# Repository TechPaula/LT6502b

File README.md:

# LT6502b
Second, slimmer, revision of my [LT6502](https://github.com/TechPaula/LT6502/tree/main) 6502 laptop.
This is very much a work in progress.

## Specs
* 65C02 running at 14MHz (hopefully)
* 46KByte of user RAM 
* EhBASIC 22p2
* eWOZMON
* Compact Flash for storage
* Built in battery (7400mAh currently)
* USB-PD Rechargable
* 10.1" Screen
* nanoSwinSID for sound (as well as beeps)

Features improved on since previous version;
* Better placement of keys
* Use an FFC for the display
* Simpler case
* Battery level indicator (CAPS Lock will flash when getting low)
* USB charge and data on single USB-C connector
* Single PCB for keyboard and logic/processor

## Images
2026-03-07 - Render of case design in progress

2026-03-21 - Picture of PCB mid assembly

## Updates
* 2026-03-21 - PCB assembly underway (power tests passed)
* 2026-03-07 - Case coming together, currently 31mm in height, vs the 70mm of the previous version)
* 2026-03-01 - PCB sent for manufacture

## In progress
* Board assembly
* Glue Logic

## To do
* Get larger display working (probably on PC6502 first)
* CPLD Glue logic working
* Firmware (removing the display parts for now as the new display uses a different driver chip)
* Keyboard/Modem code (needs a change due to using the chip directly and I need to add in serial port driver for Modem)
* Testing, lots of testing.
* Finish the case design and print it.

## Memory Map
The memory map is copied from the previous LT6502, with removal of expansion port and addition of Modem and SID

#### High Level
| Start | End | Size (Dec) | Size (Hex) | What is it | Notes |
|-------|-----|----|----|----|---------------|
| 0x0000|0xBEAF| 48816 | 0xBEB0 | RAM | This includes Zeropage and other bits BASIC may need (more below) |
| 0xBF00|0xBFFF| 512 | 0x200 | peripherals | This is where the peripherals are mapped (see below) |
| 0xC000|0xFFFF| 12288 | 0x3000 | ROM | holding EhBASIC, eWoz monitor, bootstrap and vectors |

##### ROM breakdown
| Start | End | Size (Dec) | Size (Hex) | What is it | Notes |
|-------|-----|----|----|----|---------------|
| 0xC000|0xFAFF| 15104 | 0x3B0 | EhBASIC | EhBASIC 2.22p5 |
| 0xF000|0xF2FF| 768 | 0x300 | eWozMon | [Enhanced Wozmon](https://gist.github.com/BigEd/2760560) |
| 0xF300|0xFFF9| 3322| 0xCFA | Bootstrap | startup messages and also input/output/load/save functions |
| 0xFFFA|0xFFFF| 6 | 0x0A | 6502 Vectors | |

##### RAM breakdown
| Start | End | Size (Dec) | Size (Hex) | What is it | Notes |
|-------|-----|----|----|----|---------------|
| 0x0000|0x02FF| 768 | 0x300 | RAM | This includes Zeropage and other bits BASIC may need |
| 0x0300|0x07FF| 1280 | 0x500 | RAM | This is going to be for the compact flash reading/writing |
| 0x0800|0xBDFF| 46592 | 0xB6B0 | ROM | BASIC RAM available |

##### peripherals
| Address | subAddr range | RW | What is it | Notes |
|-------|-----|----|----|---------------|
|0xBF00|00-1F|RW| nanoSwinSID | |
|0xBF20|0-1|RW| Modem | |
|0xBF30|30-9F|RW| Unused Currently | |
|0xBFAO|0-0| W| Beeper | just write 0xFF and 0x00 to turn on/off the speaker |
|0xBFBO|0-7|RW| Compact Flash |  |
|0xBFCO|0-F|RW| 65C22 |  on board VIA |
|0xBFDO|0-F|0-1| Display |   |
|0xBFEO|0-F|RW| Atmega644p | internal keyboard  |
|0xBFF0|0-1|RW| Console | FTDI USB console port   |

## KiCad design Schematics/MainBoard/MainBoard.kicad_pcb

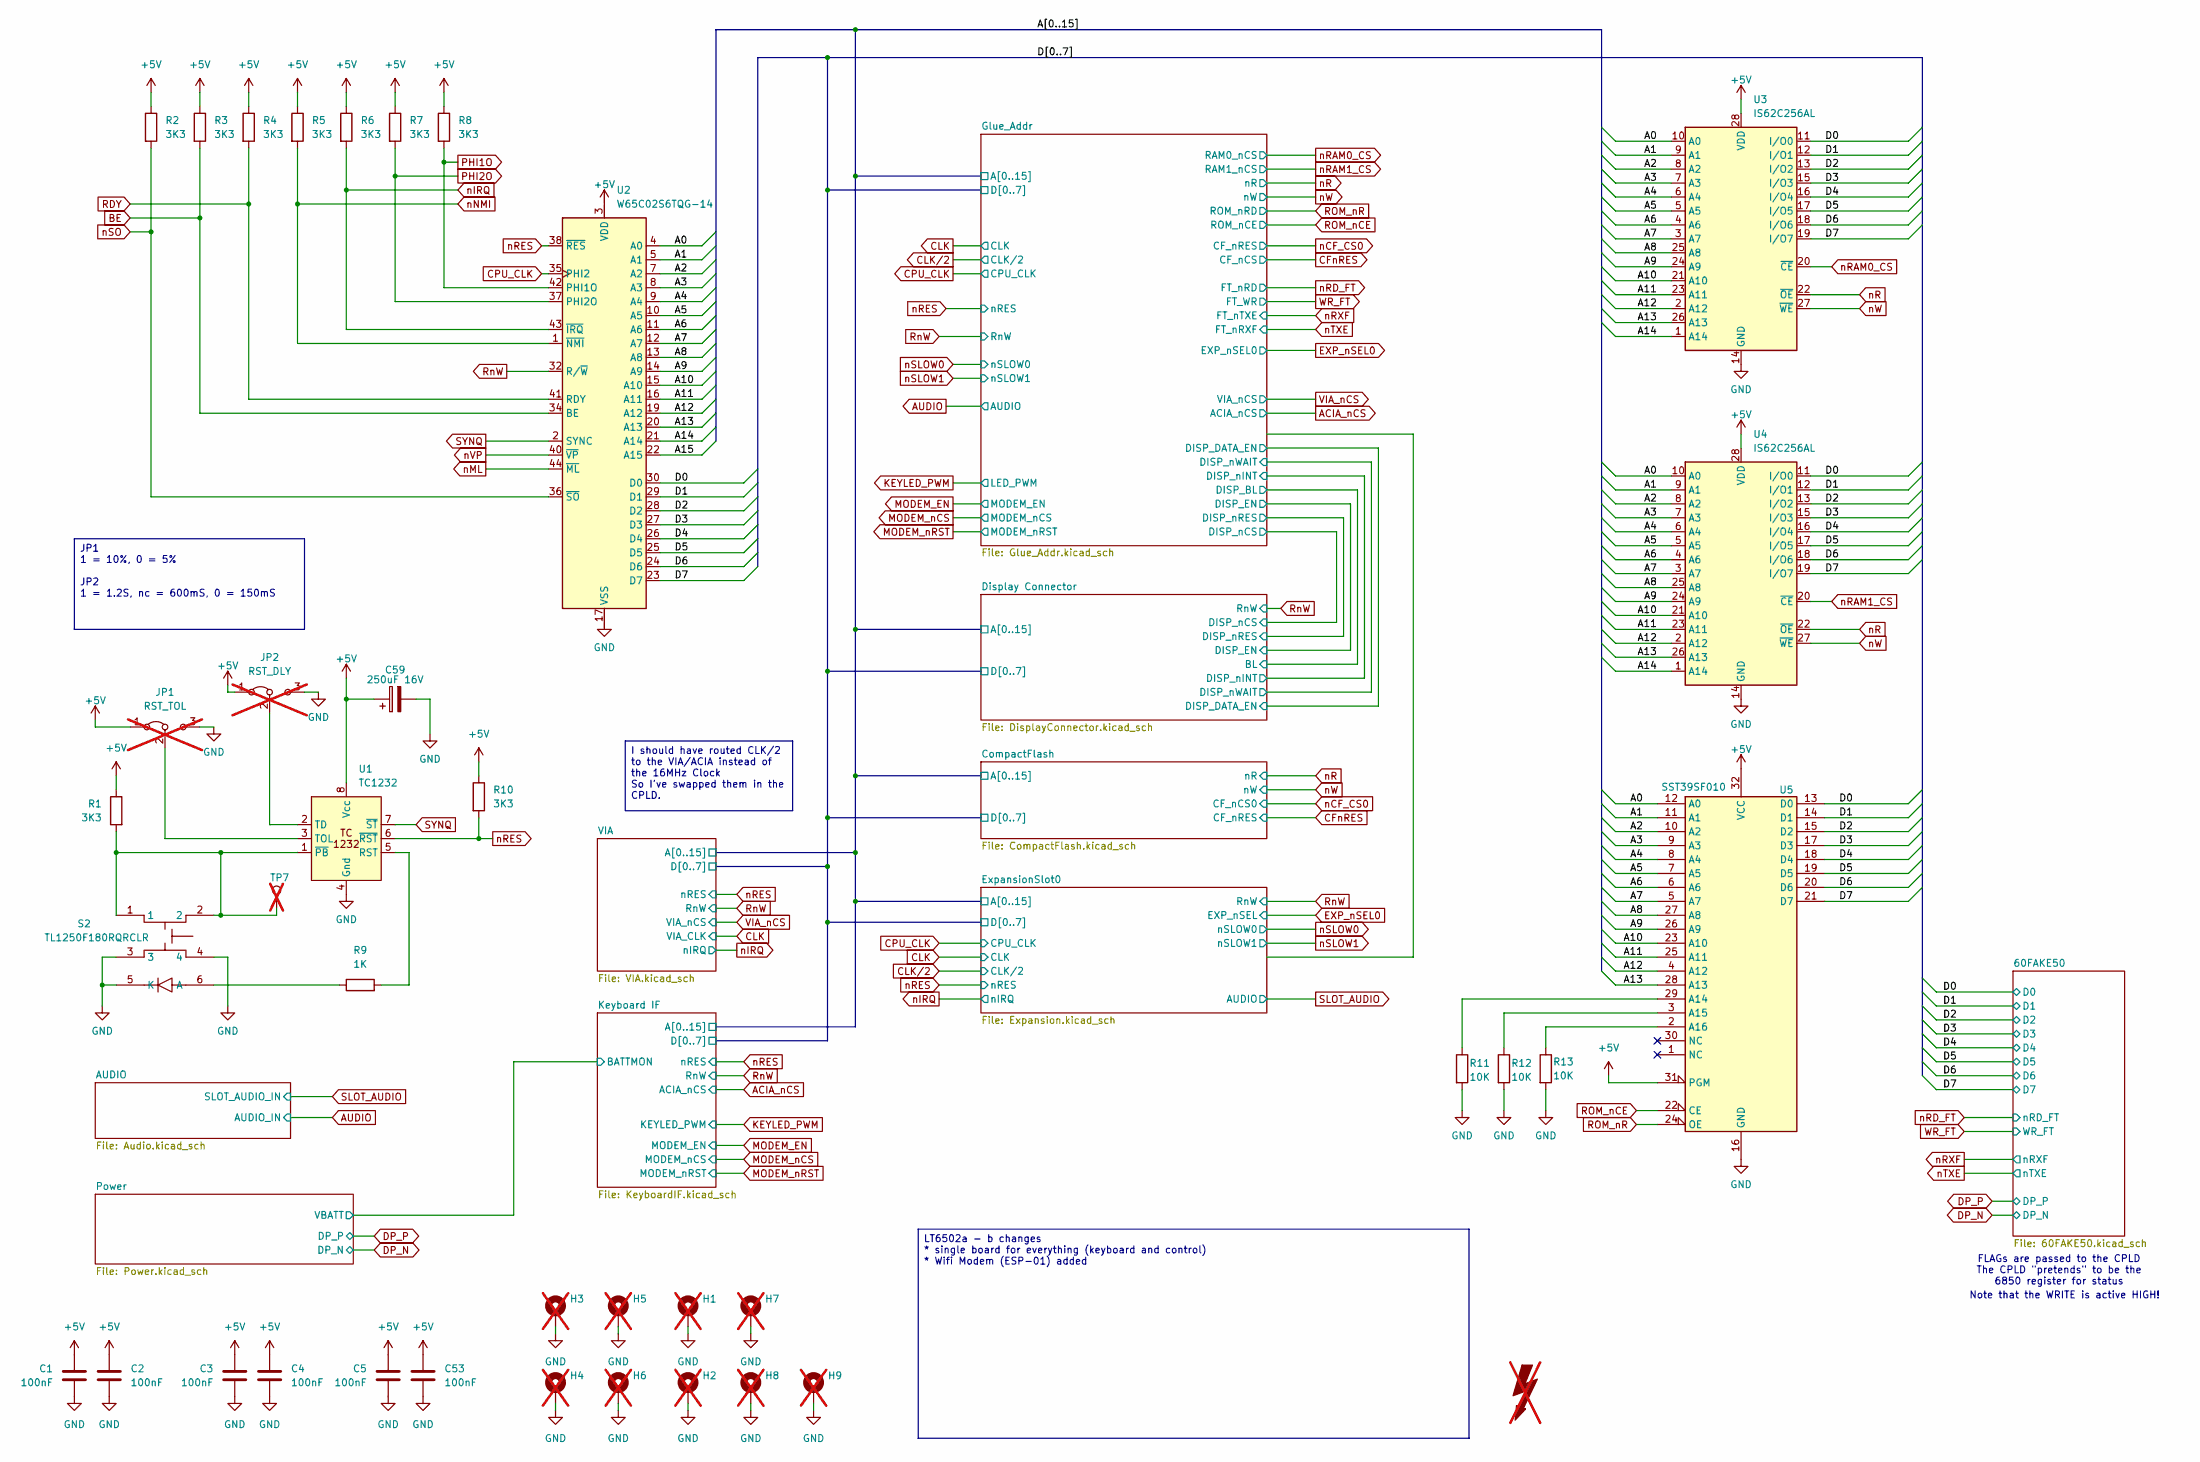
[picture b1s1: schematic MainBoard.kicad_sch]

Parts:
C1, C2, C3, C4, C5, C53: 100nF; C_0603_1608Metric; LCSC C113803
C59: 250uF 16V; CP_Elec_10x12.5; Mouser Part Number 667-EEV-FK1V681Q
FOX1: SYM_Flash_Large; Fox_avatar_18mm; LCSC DNF; not fitted
H1, H2, H3, H4, H5, H6, H7, H8, H9: MountingHole_Pad; MountingHole_3.2mm_M3_Pad_TopBottom; LCSC DNF; not fitted
JP1: RST_TOL; SolderJumper-3_P1.3mm_Bridged12_Pad1.0x1.5mm_NumberLabels; LCSC DNF; not fitted
JP2: RST_DLY; SolderJumper-3_P1.3mm_Bridged12_Pad1.0x1.5mm_NumberLabels; LCSC DNF; not fitted
R1, R2, R3, R4, R5, R6, R7, R8, R10: 3K3; R_0402_1005Metric; LCSC C25890
R9: 1K; R_0402_1005Metric; LCSC C11702
R11, R12, R13: 10K; R_0402_1005Metric; LCSC C25744
S2: TL1250F180RQRCLR; Mouser Part Number 612-TL1250F180RQRCLR
TP7: TestPoint; TestPoint_Loop_D1.80mm_Drill1.0mm_Beaded; LCSC DNF; not fitted
U1: TC1232; DIP-8_W7.62mm_LongPads; Mouser Part Number 579-TC1232CPA
U2: W65C02S6TQG-14; QFP80P1320X1320X270-44N; Mouser Part Number 955-W65C02S6TQG-14
U3, U4: IS62C256AL; SOP-28_8.4x18.16mm_P1.27mm; Mouser Part Number 870-62C256AL-25ULIT
U5: SST39SF010; DIP-32_W15.24mm_Socket; LCSC DNF

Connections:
+5V: C1.1, C2.1, C3.1, C4.1, C5.1, C53.1, C59.1, JP1.1 (A), JP2.1 (A), R1.1, R2.1, R3.1, R4.1, R5.1, R6.1, R7.1, R8.1, R10.1, U1.8 (Vcc), U2.3 (VDD), U2.31 (VDD), U3.28 (VDD), U4.28 (VDD), U5.31 (PGM), U5.32 (VCC); also elsewhere on the board
/A0: U2.4 (A0), U3.10 (A0), U4.10 (A0), U5.12 (A0); also elsewhere on the board
/A1: U2.5 (A1), U3.9 (A1), U4.9 (A1), U5.11 (A1); also elsewhere on the board
/A2: U2.7 (A2), U3.8 (A2), U4.8 (A2), U5.10 (A2); also elsewhere on the board
/A3: U2.8 (A3), U3.7 (A3), U4.7 (A3), U5.9 (A3); also elsewhere on the board
/A4: U2.9 (A4), U3.6 (A4), U4.6 (A4), U5.8 (A4); also elsewhere on the board
/A5: U2.10 (A5), U3.5 (A5), U4.5 (A5), U5.7 (A5); also elsewhere on the board
/A6: U2.11 (A6), U3.4 (A6), U4.4 (A6), U5.6 (A6); also elsewhere on the board
/A7: U2.12 (A7), U3.3 (A7), U4.3 (A7), U5.5 (A7); also elsewhere on the board
/A8: U2.13 (A8), U3.25 (A8), U4.25 (A8), U5.27 (A8); also elsewhere on the board
/A9: U2.14 (A9), U3.24 (A9), U4.24 (A9), U5.26 (A9); also elsewhere on the board
/A10: U2.15 (A10), U3.21 (A10), U4.21 (A10), U5.23 (A10); also elsewhere on the board
/A11: U2.16 (A11), U3.23 (A11), U4.23 (A11), U5.25 (A11); also elsewhere on the board
/A12: U2.19 (A12), U3.2 (A12), U4.2 (A12), U5.4 (A12); also elsewhere on the board
/A13: U2.20 (A13), U3.26 (A13), U4.26 (A13), U5.28 (A13); also elsewhere on the board
/A14: U2.21 (A14), U3.1 (A14), U4.1 (A14); also elsewhere on the board
/A15: U2.22 (A15); also elsewhere on the board
/D0: U2.30 (D0), U3.11 (I/O0), U4.11 (I/O0), U5.13 (D0); also elsewhere on the board
/D1: U2.29 (D1), U3.12 (I/O1), U4.12 (I/O1), U5.14 (D1); also elsewhere on the board
/D2: U2.28 (D2), U3.13 (I/O2), U4.13 (I/O2), U5.15 (D2); also elsewhere on the board
/D3: U2.27 (D3), U3.15 (I/O3), U4.15 (I/O3), U5.17 (D3); also elsewhere on the board
/D4: U2.26 (D4), U3.16 (I/O4), U4.16 (I/O4), U5.18 (D4); also elsewhere on the board
/D5: U2.25 (D5), U3.17 (I/O5), U4.17 (I/O5), U5.19 (D5); also elsewhere on the board
/D6: U2.24 (D6), U3.18 (I/O6), U4.18 (I/O6), U5.20 (D6); also elsewhere on the board
/D7: U2.23 (D7), U3.19 (I/O7), U4.19 (I/O7), U5.21 (D7); also elsewhere on the board
BE: R3.2, U2.34 (BE)
CPU_CLK: U2.35 (PHI2); also elsewhere on the board
GND: C1.2, C2.2, C3.2, C4.2, C5.2, C53.2, C59.2, H1.1, H2.1, H3.1, H4.1, H5.1, H6.1, H7.1, H8.1, H9.1, JP1.3 (B), JP2.3 (B), R11.2, R12.2, R13.2, S2.3, S2.4, S2.5 (K), U1.4 (Gnd), U2.17 (VSS), U2.18 (VSS), U2.39 (VSS), U3.14 (GND), U4.14 (GND), U5.16 (GND); also elsewhere on the board
unnamed: JP1.2 (C), U1.3 (TOL)
unnamed: JP2.2 (C), U1.2 (TD)
unnamed: R9.1, S2.6 (A)
unnamed: R9.2, U1.5 (RST)
unnamed: R1.2, S2.1, S2.2, TP7.1, U1.1 (~PB)
unnamed: R11.1, U5.29 (A14)
unnamed: R12.1, U5.3 (A15)
unnamed: R13.1, U5.2 (A16)
PHI1O: R8.2, U2.42 (PHI1O)
PHI2O: R7.2, U2.37 (PHI2O)
RDY: R4.2, U2.41 (RDY)
ROM_nCE: U5.22 (CE); also elsewhere on the board
ROM_nR: U5.24 (OE); also elsewhere on the board
RnW: U2.32 (R/~W); also elsewhere on the board
SYNQ: U1.7 (~ST), U2.2 (SYNC)
nIRQ: R6.2, U2.43 (~IRQ); also elsewhere on the board
nML: U2.44 (~ML)
nNMI: R5.2, U2.1 (~NMI)
nR: U3.22 (~OE), U4.22 (~OE); also elsewhere on the board
nRAM0_CS: U3.20 (~CE); also elsewhere on the board
nRAM1_CS: U4.20 (~CE); also elsewhere on the board
nRES: R10.2, U1.6 (~RST), U2.38 (~RES); also elsewhere on the board
nSO: R2.2, U2.36 (~SO)
nVP: U2.40 (~VP)
nW: U3.27 (~WE), U4.27 (~WE); also elsewhere on the board

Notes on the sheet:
FLAGs are passed to the CPLD The CPLD "pretends" to be the 6850 register for status
Note that the WRITE is active HIGH!
JP1 1 = 10%, 0 = 5% JP2 1 = 1.2S, nc = 600mS, 0 = 150mS
I should have routed CLK/2 to the VIA/ACIA instead of the 16MHz Clock So I've swapped them in the CPLD.
LT6502a - b changes * single board for everything (keyboard and control) * Wifi Modem (ESP-01) added

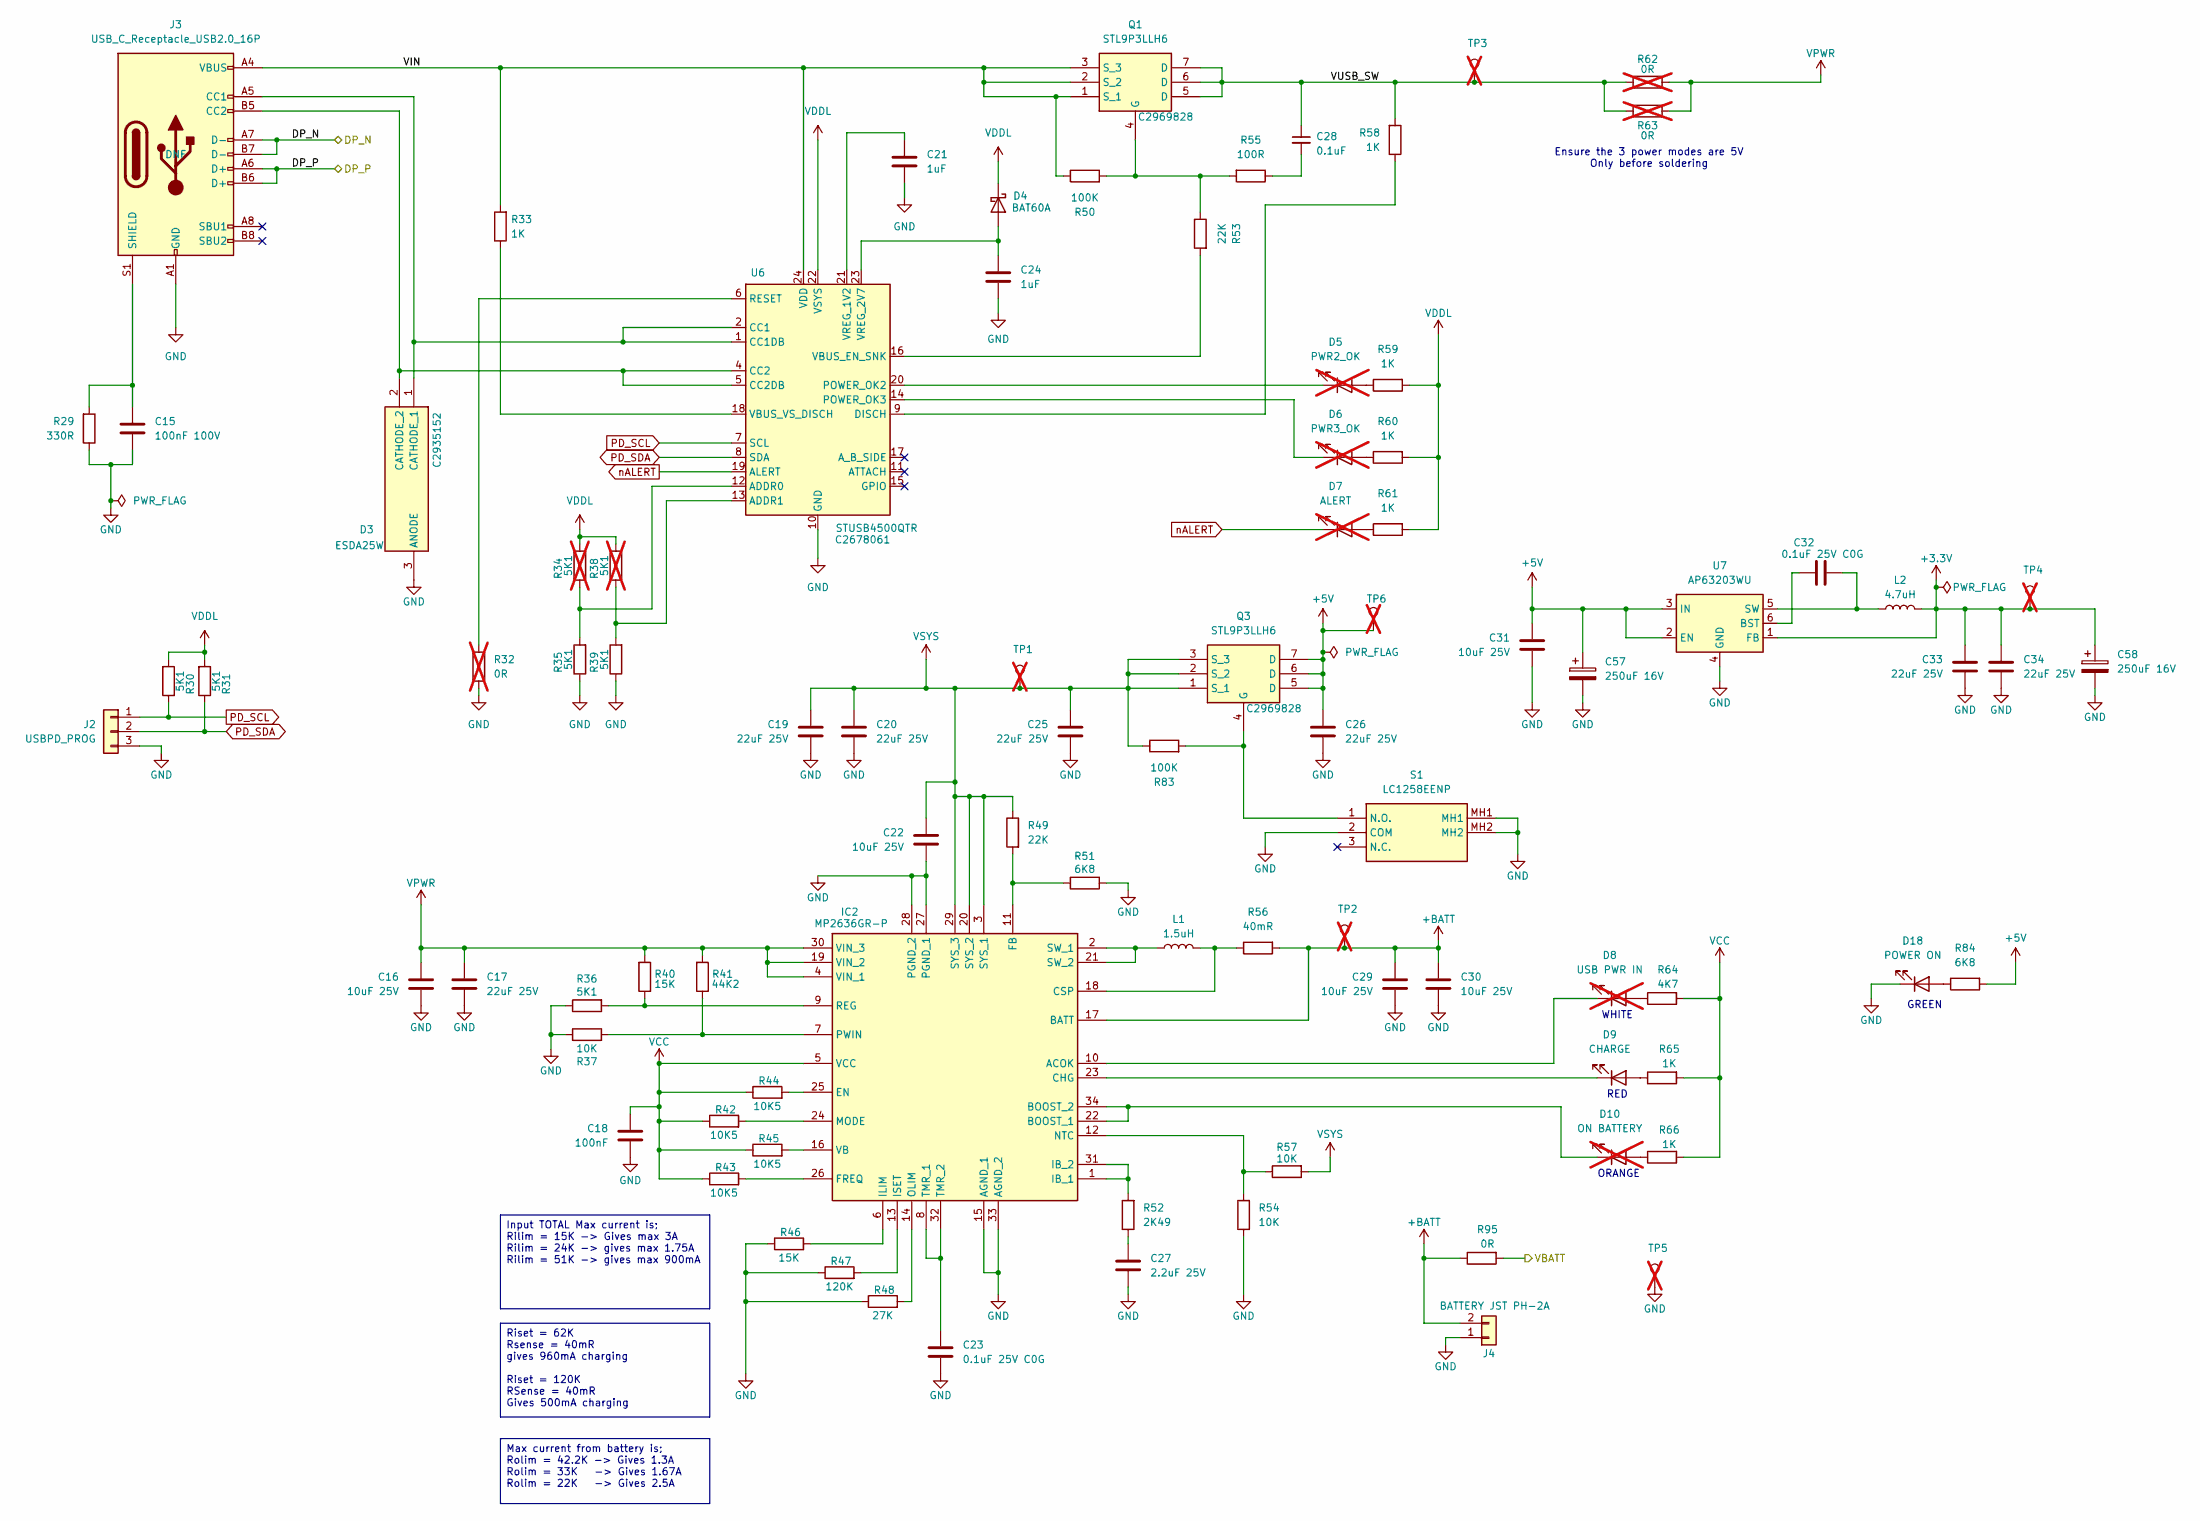
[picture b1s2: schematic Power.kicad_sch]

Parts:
C15: 100nF 100V; C_0603_1608Metric; LCSC C113803
C16, C22, C29, C30, C31: 10uF 25V; C_0805_2012Metric; LCSC C15850
C17, C19, C20, C25, C26, C33, C34: 22uF 25V; C_0805_2012Metric; LCSC C45783
C18: 100nF; C_0603_1608Metric; LCSC C113803
C21, C24: 1uF; C_0603_1608Metric; LCSC C15849
C23, C32: 0.1uF 25V C0G; C_0603_1608Metric; LCSC C91183
C27: 2.2uF 25V; C_0805_2012Metric; LCSC C19110
C28: 0.1uF; C_0603_1608Metric; LCSC C113803
C57, C58: 250uF 16V; CP_Elec_10x12.5; Mouser Part Number 667-EEV-FK1V681Q
D3: ESDA25W; SOT65P210X110-3N; Mouser Part Number 511-ESDA25W
D4: BAT60A; D_SOD-323; LCSC C5355496
D5: PWR2_OK; LED_0603_1608Metric; LCSC DNF; not fitted
D6: PWR3_OK; LED_0603_1608Metric; LCSC DNF; not fitted
D7: ALERT; LED_0603_1608Metric; LCSC DNF; not fitted
D8: USB PWR IN; LED_0805_2012Metric; LCSC DNF; not fitted
D9: CHARGE; LED_0805_2012Metric; LCSC DNF
D10: ON BATTERY; LED_0805_2012Metric; LCSC DNF; not fitted
D18: POWER ON; LED_0805_2012Metric; LCSC DNF
IC2: MP2636GR-P; MP2636GR; Mouser Part Number 946-MP2636GR-P
J2: USBPD_PROG; PinHeader_1x03_P2.54mm_Vertical; LCSC DNF
J3: USB_C_Receptacle_USB2.0_16P; USB_C_Receptacle_HCTL_HC-TYPE-C-16P-01A; LCSC DNF
J4: BATTERY JST PH-2A; SHDRRA2W80P0X250_1X2_740X1150X610P; Mouser Part Number 306-S2B-XH-ALFSN
L1: 1.5uH; INDPM6060X470N; Mouser Part Number 652-SRN6045HA-1R5Y
L2: 4.7uH; NRS5020T220MMGJV; Mouser Part Number 963-NRS5020T4R7MMGJ
Q1, Q3: STL9P3LLH6; STL20N6F7; Manufacturer_Part_Number STL9P3LLH6; Mouser Part Number 511-STL9P3LLH6
R29: 330R; R_0402_1005Metric; LCSC C25104
R30, R31, R35, R36, R39: 5K1; R_0402_1005Metric; LCSC C25905
R32: 0R; R_0402_1005Metric; LCSC DNF; not fitted
R33, R58, R59, R60, R61, R65, R66: 1K; R_0402_1005Metric; LCSC C11702
R34, R38: 5K1; R_0402_1005Metric; LCSC C25905; not fitted
R37, R54, R57: 10K; R_0402_1005Metric; LCSC C25744
R40: 15K; R_0402_1005Metric; LCSC C25756
R41: 44K2; R_0402_1005Metric; LCSC C11565
R42, R43, R44, R45: 10K5; R_0402_1005Metric; LCSC C25850
R46: 15K; R_0402_1005Metric; LCSC ???
R47: 120K; R_0402_1005Metric; LCSC ???
R48: 27K; R_0402_1005Metric
R49, R53: 22K; R_0402_1005Metric; LCSC C25768
R50, R83: 100K; R_0402_1005Metric; LCSC C25741
R51: 6K8; R_0402_1005Metric; LCSC C25917
R52: 2K49; R_0402_1005Metric; LCSC C2692737
R55: 100R; R_0402_1005Metric; LCSC C25076
R56: 40mR; R_1206_3216Metric; LCSC C2774938
R62, R63: 0R; R_0603_1608Metric; LCSC DNF; not fitted
R64: 4K7; R_0402_1005Metric
R84: 6K8; R_0402_1005Metric
R95: 0R; R_0402_1005Metric
S1: LC1258EENP; Mouser Part Number 612-LC1258EENP
TP1, TP2, TP3, TP4, TP5, TP6: TestPoint; TestPoint_Loop_D1.80mm_Drill1.0mm_Beaded; LCSC DNF; not fitted
U6: STUSB4500QTR; QFN-24-1EP_4x4mm_P0.5mm_EP2.7x2.7mm; LCSC C2678061
U7: AP63203WU; TSOT-23-6; Mouser Part Number 621-AP63203WU-7

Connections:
+3.3V: C33.1, C34.1, C58.1, L2.2, TP4.1, U7.1 (FB); also elsewhere on the board
+5V: C26.1, C31.1, C57.1, Q3.5 (D), Q3.6 (D), Q3.7 (D), R84.2, TP6.1, U7.2 (EN), U7.3 (IN); also elsewhere on the board
+BATT: C29.1, C30.1, IC2.17 (BATT), J4.2, R56.2, R95.1, TP2.1
/Keyboard IF/BATTMON: R95.2; also elsewhere on the board
/Power/VIN: J3.A4 (VBUS), J3.A9 (VBUS), J3.B4 (VBUS), J3.B9 (VBUS), Q1.1 (S_1), Q1.2 (S_2), Q1.3 (S_3), R33.2, R50.1, U6.24 (VDD)
/Power/VUSB_SW: C28.1, Q1.5 (D), Q1.6 (D), Q1.7 (D), R58.2, R62.1, R63.1, TP3.1
DP_N: J3.A7 (D-), J3.B7 (D-); also elsewhere on the board
DP_P: J3.A6 (D+), J3.B6 (D+); also elsewhere on the board
GND: C15.2, C16.2, C17.2, C18.2, C19.2, C20.2, C21.2, C22.2, C23.2, C24.2, C25.2, C26.2, C27.2, C29.2, C30.2, C31.2, C33.2, C34.2, C57.2, C58.2, D3.3 (ANODE), D18.1 (K), IC2.15 (AGND_1), IC2.27 (PGND_1), IC2.28 (PGND_2), IC2.33 (AGND_2), J2.3, J3.A1 (GND), J3.A12 (GND), J3.B1 (GND), J3.B12 (GND), J4.1, R29.1, R32.1, R35.1, R36.1, R37.1, R39.1, R46.1, R47.1, R48.1, R51.2, R54.1, S1.2 (COM), S1.MH1, S1.MH2, TP5.1, U6.10 (GND), U6.25 (GND), U7.4 (GND); also elsewhere on the board
unnamed: C27.1, R52.1
unnamed: C28.2, R55.1
unnamed: D3.1 (CATHODE_1), J3.A5 (CC1), U6.1 (CC1DB), U6.2 (CC1)
unnamed: D3.2 (CATHODE_2), J3.B5 (CC2), U6.4 (CC2), U6.5 (CC2DB)
unnamed: C24.1, D4.2 (A), U6.23 (VREG_2V7)
unnamed: D5.2 (A), R59.1
unnamed: D5.1 (K), U6.20 (POWER_OK2)
unnamed: D6.2 (A), R60.1
unnamed: D6.1 (K), U6.14 (POWER_OK3)
unnamed: D7.2 (A), R61.1
unnamed: D8.2 (A), R64.1
unnamed: D8.1 (K), IC2.10 (ACOK)
unnamed: D9.2 (A), R65.1
unnamed: D9.1 (K), IC2.23 (CHG)
unnamed: D10.2 (A), R66.1
unnamed: D10.1 (K), IC2.22 (BOOST_1), IC2.34 (BOOST_2)
unnamed: D18.2 (A), R84.1
unnamed: IC2.18 (CSP), L1.2, R56.1
unnamed: IC2.25 (EN), R44.2
unnamed: IC2.11 (FB), R49.2, R51.1
unnamed: IC2.26 (FREQ), R43.2
unnamed: IC2.1 (IB_1), IC2.31 (IB_2), R52.2
unnamed: IC2.6 (ILIM), R46.2
unnamed: IC2.13 (ISET), R47.2
unnamed: IC2.24 (MODE), R42.2
unnamed: IC2.12 (NTC), R54.2, R57.1
unnamed: IC2.14 (OLIM), R48.2
unnamed: IC2.7 (PWIN), R37.2, R41.1
unnamed: IC2.9 (REG), R36.2, R40.1
unnamed: IC2.2 (SW_1), IC2.21 (SW_2), L1.1
unnamed: C23.1, IC2.8 (TMR_1), IC2.32 (TMR_2)
unnamed: IC2.16 (VB), R45.2
unnamed: C15.1, J3.S1 (SHIELD), R29.2
unnamed: Q1.4 (G), R50.2, R53.1, R55.2
unnamed: Q3.4 (G), R83.2, S1.1 (N.O.)
unnamed: R34.1, R35.2, U6.12 (ADDR0)
unnamed: R38.1, R39.2, U6.13 (ADDR1)
unnamed: R58.1, U6.9 (DISCH)
unnamed: R32.2, U6.6 (RESET)
unnamed: R53.2, U6.16 (VBUS_EN_SNK)
unnamed: R33.1, U6.18 (VBUS_VS_DISCH)
unnamed: C21.1, U6.21 (VREG_1V2)
unnamed: C32.1, U7.6 (BST)
unnamed: C32.2, L2.1, U7.5 (SW)
PD_SCL: J2.1, R30.1, U6.7 (SCL)
PD_SDA: J2.2, R31.1, U6.8 (SDA)
VCC: C18.1, IC2.5 (VCC), R42.1, R43.1, R44.1, R45.1, R64.2, R65.2, R66.2
VPWR: C16.1, C17.1, IC2.4 (VIN_1), IC2.19 (VIN_2), IC2.30 (VIN_3), R40.2, R41.2, R62.2, R63.2; also elsewhere on the board
VSYS: C19.1, C20.1, C22.1, C25.1, IC2.3 (SYS_1), IC2.20 (SYS_2), IC2.29 (SYS_3), Q3.1 (S_1), Q3.2 (S_2), Q3.3 (S_3), R49.1, R57.2, R83.1, TP1.1
nALERT: D7.1 (K), U6.19 (ALERT)

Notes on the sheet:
Ensure the 3 power modes are 5V Only before soldering
ORANGE
RED
GREEN
WHITE
Input TOTAL Max current is; Rilim = 15K -> Gives max 3A Rilim = 24K -> gives max 1.75A Rilim = 51K -> gives max 900mA
Riset = 62K Rsense = 40mR gives 960mA charging Riset = 120K RSense = 40mR Gives 500mA charging
Max current from battery is; Rolim = 42.2K -> Gives 1.3A Rolim = 33K -> Gives 1.67A Rolim = 22K -> Gives 2.5A

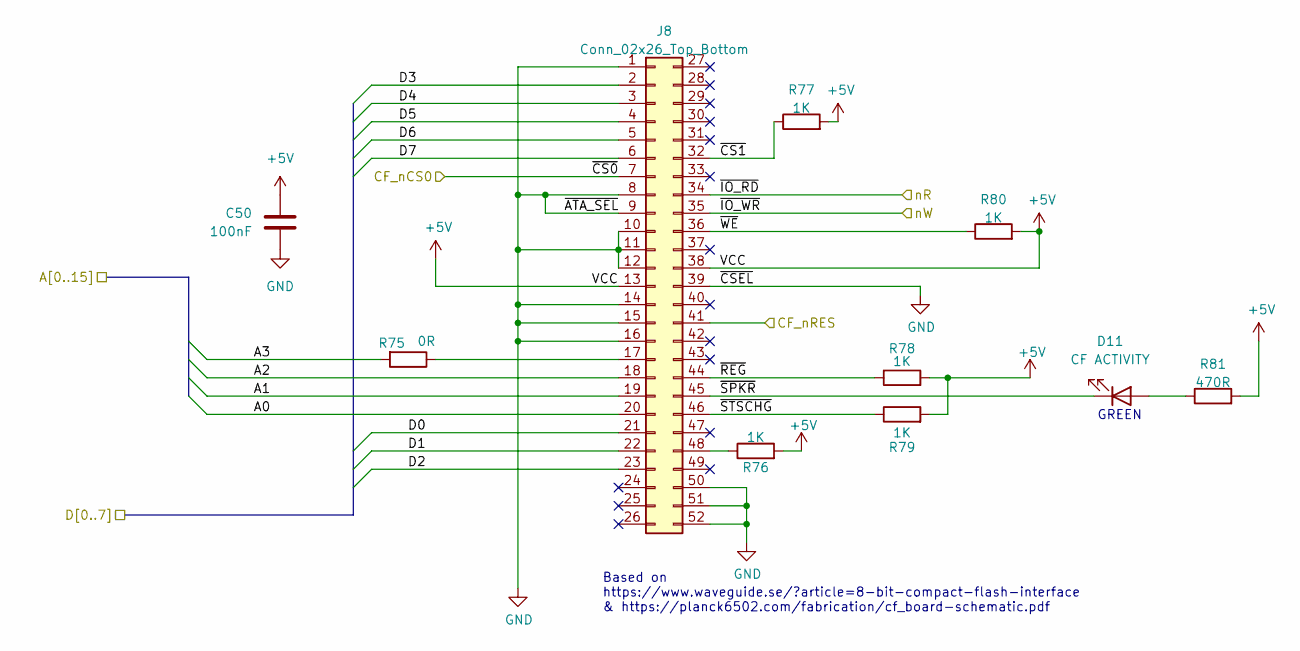
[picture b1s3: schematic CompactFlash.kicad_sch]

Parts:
C50: 100nF; C_0402_1005Metric; LCSC C113803
D11: CF ACTIVITY; LED_0805_2012Metric; LCSC DNF
J8: Conn_02x26_Top_Bottom; SD-SMD_CFH-L3C1LBL01MN0; Mouser Part Number 710-693120035011; LCSC DNF
R75: 0R; R_0402_1005Metric; LCSC DNF
R76, R77, R78, R79, R80: 1K; R_0402_1005Metric; LCSC C11702
R81: 470R; R_0402_1005Metric; LCSC C25117

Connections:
+5V: C50.1, J8.13, J8.38, R76.2, R77.2, R78.2, R79.2, R80.2, R81.2; also elsewhere on the board
/A0: J8.20; also elsewhere on the board
/A1: J8.19; also elsewhere on the board
/A2: J8.18; also elsewhere on the board
/A3: R75.2; also elsewhere on the board
/CompactFlash/~CS1: J8.32, R77.1
/CompactFlash/~REG: J8.44, R78.1
/CompactFlash/~SPKR: D11.1 (K), J8.45
/CompactFlash/~STSCHG: J8.46, R79.1
/CompactFlash/~WE: J8.36, R80.1
/D0: J8.21; also elsewhere on the board
/D1: J8.22; also elsewhere on the board
/D2: J8.23; also elsewhere on the board
/D3: J8.2; also elsewhere on the board
/D4: J8.3; also elsewhere on the board
/D5: J8.4; also elsewhere on the board
/D6: J8.5; also elsewhere on the board
/D7: J8.6; also elsewhere on the board
CFnRES: J8.41; also elsewhere on the board
GND: C50.2, J8.1, J8.8, J8.9, J8.10, J8.11, J8.12, J8.14, J8.15, J8.16, J8.39, J8.50, J8.51, J8.52; also elsewhere on the board
unnamed: D11.2 (A), R81.1
unnamed: J8.17, R75.1
unnamed: J8.48, R76.1
nCF_CS0: J8.7; also elsewhere on the board
nR: J8.34; also elsewhere on the board
nW: J8.35; also elsewhere on the board

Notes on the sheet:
GREEN
Based on https://www.waveguide.se/?article=8-bit-compact-flash-interface & https://planck6502.com/fabrication/cf_board-schematic.pdf

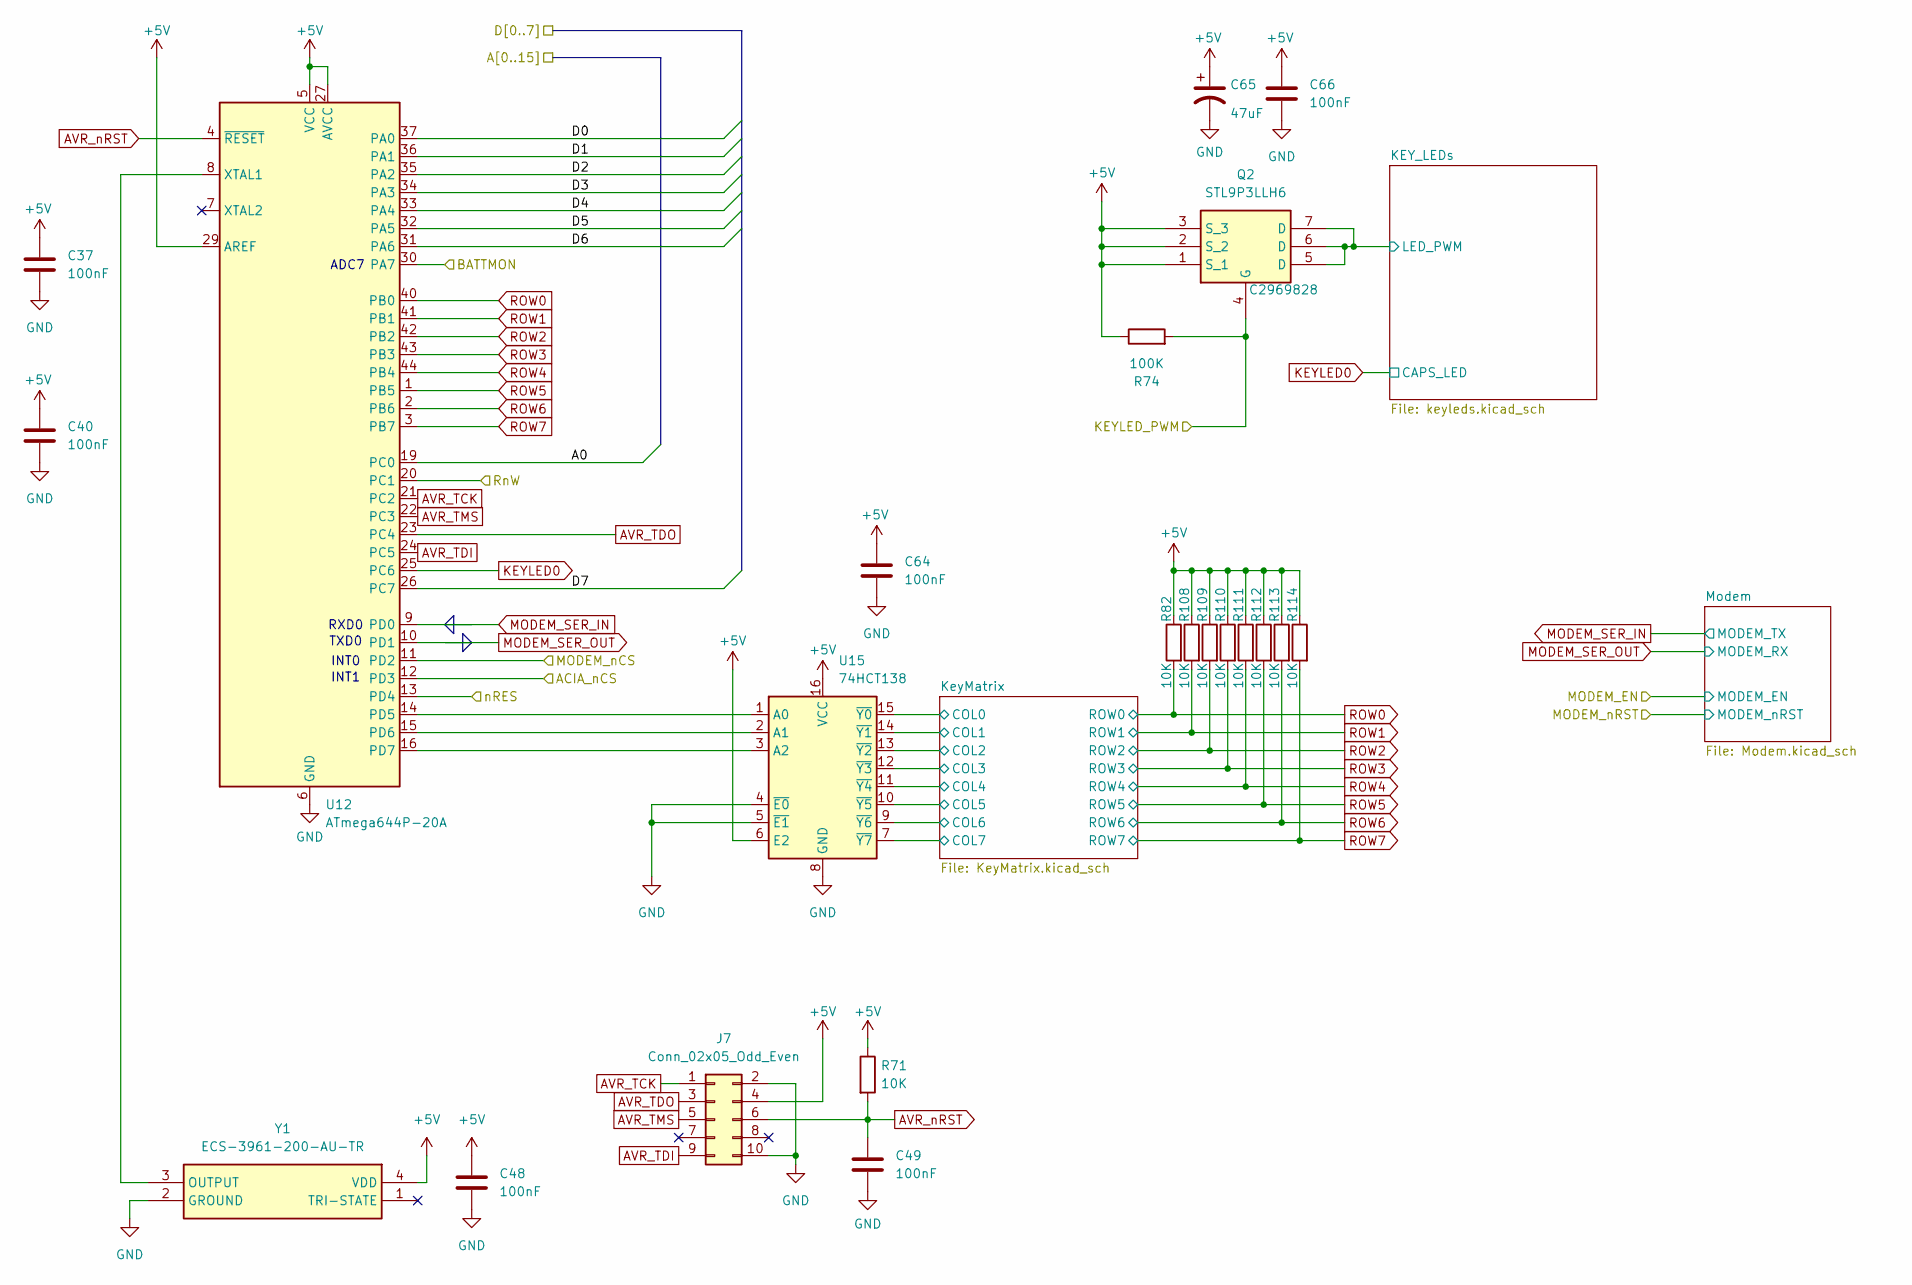
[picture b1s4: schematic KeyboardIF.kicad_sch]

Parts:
C37, C40, C49, C64, C66: 100nF; C_0805_2012Metric; LCSC C49678
C48: 100nF; C_0402_1005Metric; LCSC C113803
C65: 47uF; C_1206_3216Metric; LCSC C96123
J7: Conn_02x05_Odd_Even; PinHeader_2x05_P2.54mm_Horizontal; LCSC DNF
Q2: STL9P3LLH6; STL20N6F7; Manufacturer_Part_Number STL9P3LLH6; Mouser Part Number 511-STL9P3LLH6
R71, R82, R108, R109, R110, R111, R112, R113, R114: 10K; R_0603_1608Metric_Pad0.98x0.95mm_HandSolder; LCSC DNF
R74: 100K; R_0402_1005Metric; LCSC DNF
U12: ATmega644P-20A; TQFP-44_10x10mm_P0.8mm
U15: 74HCT138; SSOP-16_5.3x6.2mm_P0.65mm; LCSC C8115
Y1: ECS-3961-200-AU-TR; ECS3961200AUTR; Mouser Part Number 520-3961-200-AUT

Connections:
+5V: C37.1, C40.1, C48.1, C64.1, C65.1, C66.1, J7.4, Q2.1 (S_1), Q2.2 (S_2), Q2.3 (S_3), R71.1, R74.1, R82.1, R108.1, R109.1, R110.1, R111.1, R112.1, R113.1, R114.1, U12.5 (VCC), U12.17 (VCC), U12.27 (AVCC), U12.29 (AREF), U12.38 (VCC), U15.6 (E2), U15.16 (VCC), Y1.4 (VDD); also elsewhere on the board
/A0: U12.19 (PC0); also elsewhere on the board
/D0: U12.37 (PA0); also elsewhere on the board
/D1: U12.36 (PA1); also elsewhere on the board
/D2: U12.35 (PA2); also elsewhere on the board
/D3: U12.34 (PA3); also elsewhere on the board
/D4: U12.33 (PA4); also elsewhere on the board
/D5: U12.32 (PA5); also elsewhere on the board
/D6: U12.31 (PA6); also elsewhere on the board
/D7: U12.26 (PC7); also elsewhere on the board
/Keyboard IF/BATTMON: U12.30 (PA7); also elsewhere on the board
/Keyboard IF/KEY_LEDs/LED_PWM: Q2.5 (D), Q2.6 (D), Q2.7 (D); also elsewhere on the board
/Keyboard IF/KeyMatrix/COL0: U15.15 (~Y0); also elsewhere on the board
/Keyboard IF/KeyMatrix/COL1: U15.14 (~Y1); also elsewhere on the board
/Keyboard IF/KeyMatrix/COL2: U15.13 (~Y2); also elsewhere on the board
/Keyboard IF/KeyMatrix/COL3: U15.12 (~Y3); also elsewhere on the board
/Keyboard IF/KeyMatrix/COL4: U15.11 (~Y4); also elsewhere on the board
/Keyboard IF/KeyMatrix/COL5: U15.10 (~Y5); also elsewhere on the board
/Keyboard IF/KeyMatrix/COL6: U15.9 (~Y6); also elsewhere on the board
/Keyboard IF/KeyMatrix/COL7: U15.7 (~Y7); also elsewhere on the board
ACIA_nCS: U12.12 (PD3); also elsewhere on the board
AVR_TCK: J7.1, U12.21 (PC2)
AVR_TDI: J7.9, U12.24 (PC5)
AVR_TDO: J7.3, U12.23 (PC4)
AVR_TMS: J7.5, U12.22 (PC3)
AVR_nRST: C49.1, J7.6, R71.2, U12.4 (~RESET)
GND: C37.2, C40.2, C48.2, C49.2, C64.2, C65.2, C66.2, J7.2, J7.10, U12.6 (GND), U12.18 (GND), U12.28 (GND), U12.39 (GND), U15.4 (~E0), U15.5 (~E1), U15.8 (GND), Y1.2 (GROUND); also elsewhere on the board
KEYLED0: U12.25 (PC6); also elsewhere on the board
KEYLED_PWM: Q2.4 (G), R74.2; also elsewhere on the board
MODEM_SER_IN: U12.9 (PD0); also elsewhere on the board
MODEM_SER_OUT: U12.10 (PD1); also elsewhere on the board
MODEM_nCS: U12.11 (PD2); also elsewhere on the board
unnamed: U12.14 (PD5), U15.1 (A0)
unnamed: U12.15 (PD6), U15.2 (A1)
unnamed: U12.16 (PD7), U15.3 (A2)
unnamed: U12.8 (XTAL1), Y1.3 (OUTPUT)
ROW0: R82.2, U12.40 (PB0); also elsewhere on the board
ROW1: R108.2, U12.41 (PB1); also elsewhere on the board
ROW2: R109.2, U12.42 (PB2); also elsewhere on the board
ROW3: R110.2, U12.43 (PB3); also elsewhere on the board
ROW4: R111.2, U12.44 (PB4); also elsewhere on the board
ROW5: R112.2, U12.1 (PB5); also elsewhere on the board
ROW6: R113.2, U12.2 (PB6); also elsewhere on the board
ROW7: R114.2, U12.3 (PB7); also elsewhere on the board
RnW: U12.20 (PC1); also elsewhere on the board
nRES: U12.13 (PD4); also elsewhere on the board

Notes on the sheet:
INT0
INT1
ADC7
TXD0
RXD0
